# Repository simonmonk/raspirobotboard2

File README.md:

Source code for use with the RaspiRobot Board V2.

**Note that if you are looking for version 1 of this board, please see:**

https://github.com/simonmonk/raspirobotboard

***Both version 1 and version 2 of the RasPiRobot Board work just fine with the new Raspberry Pi2 and the Model B+***

# Support
If you need any help with the software or board please contact linda@monkmakes.com or leave a comment on monkmakes.com

# Introduction

Version 2 of the RaspiRobot Board (RRB2) has learnt by the feedback from version 1 and it is a great improvement. 

The main features of version 2 are listed below. Changes from version 1 are highlighted in bold:
+ **Supplied fully assembled - no soldering**
+ Bi-directional control of two motors
+ **Variable (PWM) power control**. This allows you to both control the speed of the motors independently. 
+ **Supplies the Raspberry Pi with upto 2A using a switch mode power supply - run a fully loaded Pi and the Robot from 6 x AA batteries**
+ **Rangefinder header socket directly compatible with cheap HC-SR-04 ultrasonic range finders. Just plug them in directly**
+ **5V I2C header, pin compatible with Adafruit displays**
+ Two buffered open collector outputs
+ Two LEDs
+ Two switch inputs
+ Screw terminals for motors and battery

# How it Works

The diagram below shows how an RRB2 board is used. The RRB2 is powered from a battery pack that needs to be between 6 and 12V DC. Although using 4 x AA batteries can in theory provide 6V, actually the battery voltage will usually quickly fall below that, so it it better to use at least 6 x AA batteries, either rechargeable or regular heavy duty batteries. A 7.2V LiPo battery pack will also work just fine.

Note that you don't need a separate power supply for the Raspberry Pi. The RRB2 will provide 5V at 2A with ease to the Raspberry Pi, and motors. 

Note that 6V motor will usually work just fine at 5V.

# Installing the Python Libraries

On your Raspberry Pi, issue the following commands in a Terminal window:

```
$ wget https://github.com/simonmonk/raspirobotboard2/raw/master/python/dist/rrb2-1.1.tar.gz
$ tar -xzf rrb2-1.1.tar.gz
$ cd rrb2-1.1
$ sudo python setup.py install
```

Attach the RRB2 to your Raspberry Pi. You do not need to attach batteries, motors or anything else to the RRB2 just yet. For now you can just power it through the Pi's normal USB power connector.

Lets run some tests from the Python Console now that everything is installed. We can experiment with the RaspiRobot Board v2, even without any motors 

Open a Python console (Python2 not 3) by typing the following into a Terminal window:
`$ sudo python`

Then, within the python console, type the following, one line at a time:

```
from rrb2 import *
rr = RRB2()
rr.set_led1(1)
rr.set_led1(0)
rr.set_led2(1)
rr.set_led2(0)
rr.sw1_closed()
```

The last step should display the answer "False" because no switch is attached.

If you prefer, you can use True and False in place of 1 and 0 in the examples above.

# Connect a Battery and Motors

The quickest way to use the RRB2 as a roving robot is to buy a robot chassis such as the Magician Chassis (available from many sources) or similar low-cost robot chassis kits from eBay. These kits come as a laser cut body, a pair of gearmotors, often a battery box and nuts and bolts to fix it all together.

Here is one such chassis. The first step is to bolt this all together. Note that these are usually supplied with a 4 x AA battery box. You will need to swap this for a similar 6 x AA battery box or a 7.2V LiPo battery pack. Rechargeable batteries are a good idea when driving motors.

Once the chassis is built, use some of the bolts suppled to fix the Raspberry Pi on the chassis and then attach the RRB2 onto the GPIO connector. Make sure its the right way arround, and that all the pins meet up with the socket.

The leads from the motors will thread up through the chassis and each pair of leads should go to one of the two screw terminals labelled L and R for (left and right). If you put the leads in the wrong way around, the direction of the motor will be opposite to that expected, so just swap them over if this happens.

Next, make sure that your Raspberry Pi's USB power lead is unplugged. From now on we are going to power it from batteries.

**WARNING: Never power the Raspberry Pi from both batteries and the USB power connector. One or other, but NOT both.**

It is a good idea to leave the wheels off the robot chassis for now so that it does not unexpectedly drive itself off your table. One or both of the motors may spin as the Raspberry Pi starts up.

Wire the battery pack into the third pair of screw terminals. +V towards the outside of the board. The Raspberry Pi's power light should light up and it will start to boot. LED1 and LED2 on the RRB2 will also light up.

Having your Pi set up for WiFi will allow you to connect to it wirelessly [over SSH](http://learn.adafruit.com/adafruits-raspberry-pi-lesson-6-using-ssh/overview). So, you may want to plug in a USB WiFi dongle.

# API Reference

## General
The library implements a class called RRB2. This is only available for Python 2 and any Python programs that you write that use the libaray must be run as a super user. I.e.

`sudo python myProgram.py'

To import the library and create an instance of the class, put this at the top of your Python program.

```
from rrb2 import *
rr = RRB2()
```

If you have an older revision 1 Raspberry Pi, then you need to do this instead:

```
from rrb2 import *
rr = RRB2(revision=1)
```

The rest is pretty straightforward, there are just a load of useful methods on the class that you can use.

## LEDs

There are two LEDs built-in to the RaspiRobotBoard, called LED1 and LED2. Both of these can be turned on and off using the following methods:

To turn LED1 on just do:

`rr.set_led1(1)`

To turn it off again do:

`rr.set_led1(0)`

To control LED2 just do the same thing but using setLED2.

## Switch Inputs

The sw1_closed() and sw2_closed() functions return true if the contacts for that switch are closed. By default, the switches are open. You can test out closing the switch by shorting the two contacts with a screwdriver.

The following test program will show you the state of each of the switch contacts.

```
from rrb2 import *

rr = RRB2()

while True:
    print("SW1=" + str(rr.sw1_closed()) + " SW2=" + str(rr.sw2_closed()))
    raw_input("check again")
```

## Open Collector Outputs

The RaspiRobotBoard has two low-power open collector outputs. These can each source up to 25mA and so are suitable for driving LEDs with series resistors. They can also be used to drive transistors and other external electronics. They are buffered and therefore protect the Raspberry Pi' s processor.

To turn the Open Collector OC1 output on just do:

`rr.set_oc1(1)`

To turn it off again do: 

`rr.set_oc1(0)`

To control OC2, substitute oc2 in place of oc1 in the examples above

## Motor (High Level Interface)

There are two levels of command for controlling the motors. There is a high level interface that assumes that the motors are connected to wheels on a rover. These commands are forward, reverse, left, right and stop.

`rr.forward()`

... will start both motors running in the same direction to move the robot rover forwards. They will continue in this direction until another command is issued.

If you want to move forward for a certain amount of time, you can specify a number of seconds as an optional first argument. If you supply a second parameter between 0 and 1 this will control the speed of the motor. This is set to 0.5 as a defaut. If you want the motors to run indefinately, but also want to control the speed, then use 0 as the first patrameter.

Some examples:

```
rr.forward()       # forward half speed indefinately
rr.forward(5)      # forward for 5 seconds at half speed
rr.forward(5, 1)   # forward for 5 seconds at full speed
```

The commands left, right and reverse all work in the same way.

The stop command stops all the motors.

## Motor (Low Level Interface)

The low level interface is intended for control of the motors directly. It allows you to control the speed of each motor and its direction independently.

The method for this (set_motors) takes four arguments: the left speed, left motor direction, right spped and direction.

So to set both motors going forward at full speed, you would just use the following:

`rr.set_motors(1, 0, 1, 0)`

.. and half speed would be:

`rr.set_motors(0.5, 0, 0.5, 0)`

to send the motors both at half speed in opposite directions is:

`rr.set_motors(0.5, 1, 0.5, 0)`

## Range Finder

If you fit the RRB2 with an SR-04 ultrasonic rangefinder, then you can use the following call to measure the distance to the enarest obstacle in cm.

`rr.get_distance()`

## Hardware

The RRB2 uses the following pins:

    LEFT_GO_PIN = 17
    LEFT_DIR_PIN = 4
    RIGHT_GO_PIN = 10
    RIGHT_DIR_PIN = 25   
    SW1_PIN = 11
    SW2_PIN = 9
    LED1_PIN = 7
    LED2_PIN = 8
    OC1_PIN = 22
    OC2_PIN = 27
    OC2_PIN_R1 = 21 (rev 1) or 27 rev 2
    TRIGGER_PIN = 18
    ECHO_PIN = 23

The LEDs and OC outputs are buffered. The switch inputs are not.

You can find the EAGLE design files in the "hardware" section of tis repo.

# Using I2C Displays

The I2C socket is pin compatible with these Adafruit displays: 
+ [4 Digit 7-segment display (red)](http://www.adafruit.com/products/878)
+ [Mini 8x8 LED Matrix (red)](http://www.adafruit.com/products/870)
+ [Bi-color 8x8 LED Matrix (red)](http://www.adafruit.com/products/902)

To use these you will need to download Adafruit's Python library for the Pi from [here](http://learn.adafruit.com/matrix-7-segment-led-backpack-with-the-raspberry-pi/overview).

Make sure that you plug the display in the right way around. The socket pins are labelled on the RRB2, make sure they match up with the labels on the display. You can use male to female jumper wires if you wish to put the display further away or its too big.

# Example Projects

Have a look in the "examples" folder of this library for some examples using the RRB2.

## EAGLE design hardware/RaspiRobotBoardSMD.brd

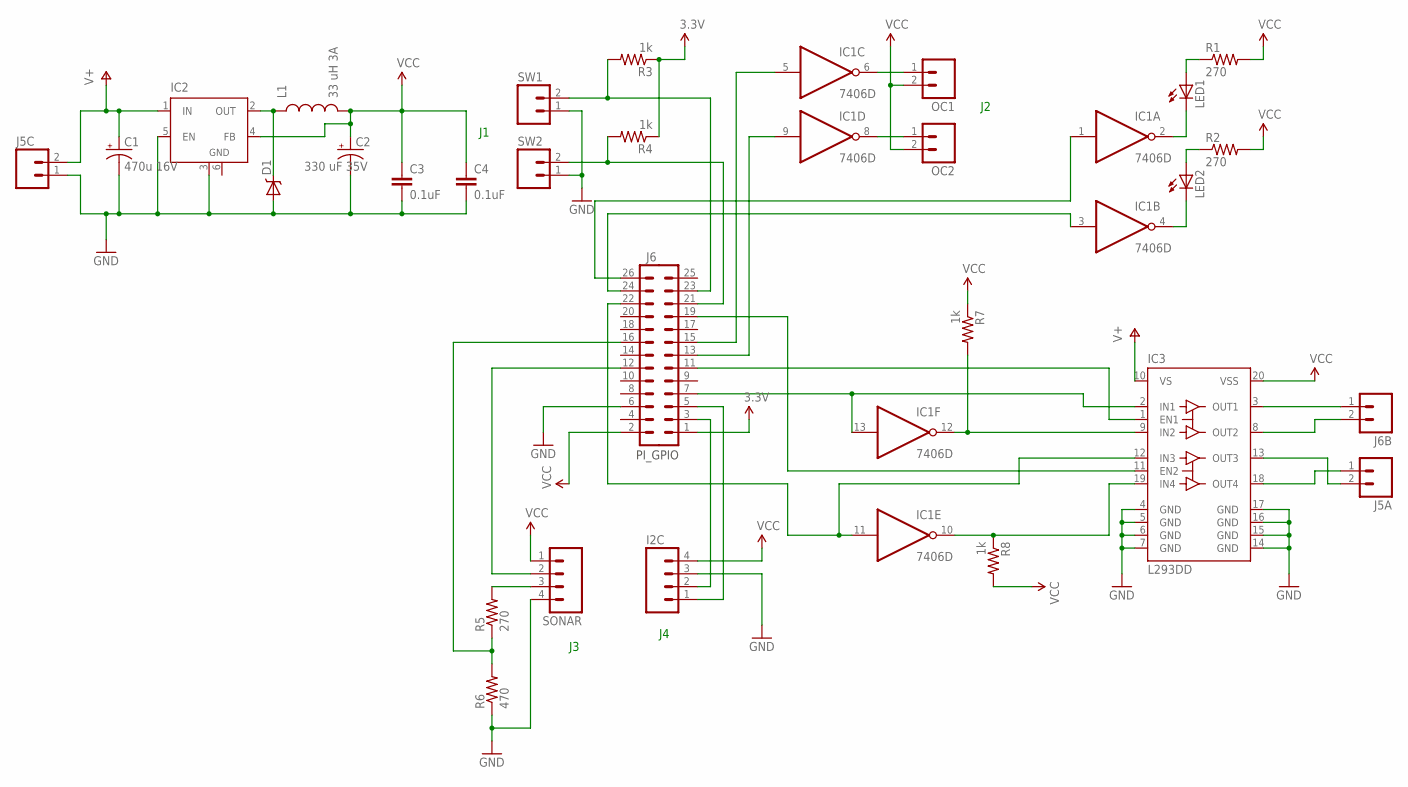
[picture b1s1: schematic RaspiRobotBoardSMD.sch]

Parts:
C1: 470u 16V; PANASONIC_E
C2: 330 uF 35V; PANASONIC_G
C3, C4: 0.1uF; 0805
D1: B340A; SMA-DIODE
I2C: M04PTH; 1X04
IC1: 7406D; SO14
IC2: LM2596S; TO263-5
IC3: L293DD; SO20
J5A, J5C, J6B: M023.5MM_LOCK; SCREWTERMINAL-3.5MM-2_LOCK
J6: M13X22X13; 2X13
L1: 33 uH 3A; CDRH125
LED1, LED2: LEDSMT1206; 1206
OC1, OC2: M02PTH; 1X02
R1, R2, R5: 270; 0805
R3, R4, R7, R8: 1k; 0805
R6: 470; 0805
SONAR: M04PTH; 1X04
SW1, SW2: M02PTH; 1X02

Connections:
3.3V: J6.1, R3.1, R4.1
GND: C1.-, C2.-, C3.2, C4.2, D1.A, I2C.3, IC1.7 (GND), IC2.3 (GND), IC2.5 (EN), IC2.6 (GND), IC3.4 (GND), IC3.5 (GND), IC3.6 (GND), IC3.7 (GND), IC3.14 (GND), IC3.15 (GND), IC3.16 (GND), IC3.17 (GND), J5C.1, J6.6, R6.1, SONAR.4, SW1.1, SW2.1
unnamed: D1.C, IC2.2 (OUT), L1.1
unnamed: IC3.3 (OUT1), J6B.1
unnamed: IC3.8 (OUT2), J6B.2
unnamed: IC3.18 (OUT4), J5A.1
unnamed: IC1.13 (I), IC3.2 (IN1), J6.7
unnamed: IC1.12 (O), IC3.9 (IN2), R7.2
unnamed: IC1.10 (O), IC3.19 (IN4), R8.1
unnamed: IC1.11 (I), IC3.12 (IN3), J6.22
unnamed: LED1.A, R1.1
unnamed: LED2.A, R2.1
unnamed: IC1.2 (O), LED1.C
unnamed: IC1.4 (O), LED2.C
unnamed: IC1.6 (O), OC1.1
unnamed: IC1.8 (O), OC2.1
unnamed: J6.23, R3.2, SW1.2
unnamed: J6.21, R4.2, SW2.2
unnamed: IC1.3 (I), J6.24
unnamed: J6.16, R5.1, R6.2
unnamed: J6.12, SONAR.2
unnamed: R5.2, SONAR.3
unnamed: IC1.1 (I), J6.26
unnamed: IC3.1 (EN1), J6.11
unnamed: IC3.11 (EN2), J6.19
unnamed: IC1.9 (I), J6.13
unnamed: IC1.5 (I), J6.15
unnamed: I2C.2, J6.3
unnamed: I2C.1, J6.5
unnamed: IC3.13 (OUT3), J5A.2
V+: C1.+, IC2.1 (IN), IC3.10 (VS), J5C.2
VCC: C2.+, C3.1, C4.1, I2C.4, IC1.14 (VCC), IC2.4 (FB), IC3.20 (VSS), J6.2, L1.2, OC1.2, OC2.2, R1.2, R2.2, R7.1, R8.2, SONAR.1

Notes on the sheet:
PI_GPIO

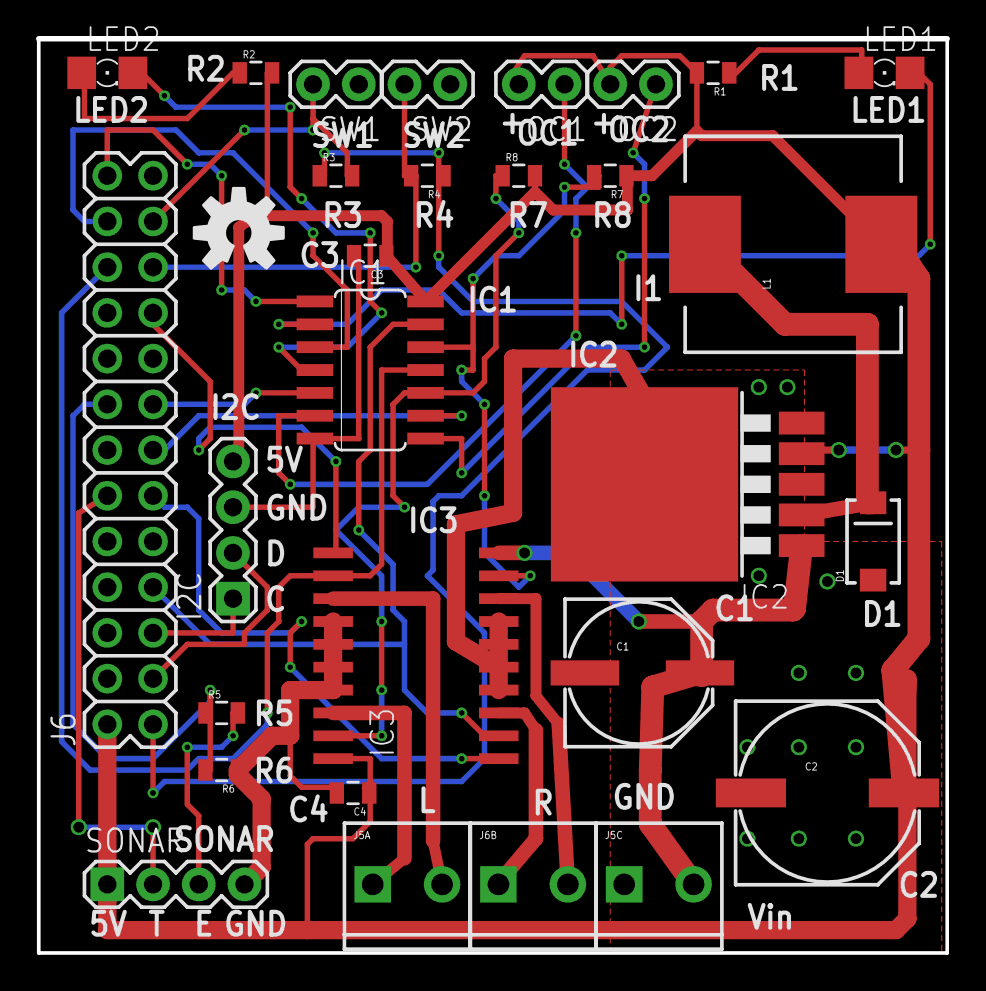
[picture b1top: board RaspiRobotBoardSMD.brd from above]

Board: 2 copper layers, 50.5 x 50.8 mm, 30 parts (0 on the bottom side), 32 nets.

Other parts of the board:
U$1: OSHW-LOGO-M

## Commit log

2014-02-13 Delete test_suite.py
    renamed to test ready for changing
2014-02-13 changed library file name
2014-02-13 fixes for test prog
2014-02-13 modified test program
2014-02-13 added pwm to motors
2014-03-15 Create README.html
    experiment
2014-03-24 Update rrb2.py
    added speed to forward, back etc
2014-03-24 added EAGLE files
2014-05-27 fixed installer problem
2014-05-27 Update README.md
    updated for tarball install and 1.1
2014-10-27 add stepper example
2015-06-27 added schematic

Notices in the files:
parts and their libraries:
SparkFun-Connectors: Licensing: CC v3.0 Share-Alike You are welcome to use this library for commercial purposes.
